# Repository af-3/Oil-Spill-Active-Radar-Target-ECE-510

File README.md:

# Oil-Spill-Active-Radar-Target-ECE-510
Cooperating radar target design for Portland State University ECE 510 winter 2016 Class<br>
[Radar Equations google Dock](https://docs.google.com/spreadsheets/d/1SBJ6qjm3yuyV2hIqerSS4fywFo_I5tQoiRfdYXWfvTU/pubhtml)

##Requirements
 * Must
   * Have a detection range of 10 meters
   * Be enviromentaly friendy specifically marine friendy
   * Build 8 working targets, but support at least 64 targets
   * Function correctly for at least 48 hours
   * Software must detect at least 64 targets
 * Should
   * Be no bigger then 3 X 3 X 2 inches
   * Have a detection range of 100 meters 
 * Could
   * Have smart tracking capability

##Additional Notes
 * Radar transmitter output power -6.02 dBm (.25 mW)
 * Radar operating frequincy is 2.304080 GHz
 * Antenna beam width on the vertical axis is about 68 digrees
 * Antenna beam width on the horizontal axis is about 52 digrees
 * Measured Receiver noise Floor is -120 dBm (10^-15 W)

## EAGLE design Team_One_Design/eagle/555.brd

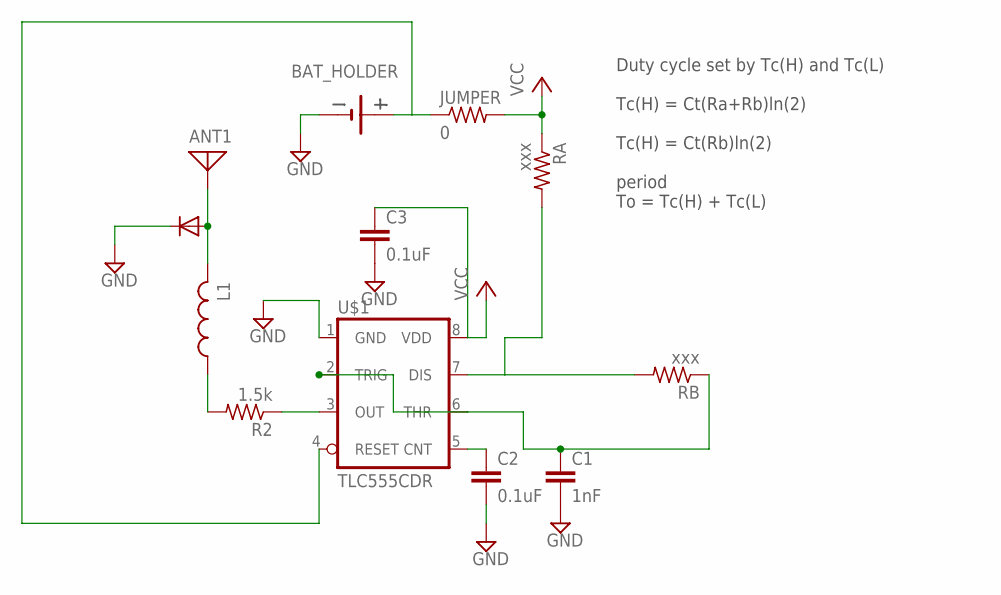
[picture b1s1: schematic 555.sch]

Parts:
ANT1: ANTENNA; PAD-01
C1: 1nF; C050-024X044
C2, C3: 0.1uF; C050-024X044
JUMPER: 0; R0805
L1: L-USL2012C; L2012C
R2: 1.5k; R0805
RA: xxx; R0805
RB: xxx; R0805
U$1: TLC555CDR; TLC555CRD
U$2: BAT_HOLDER
U$3: BAT-15-03W

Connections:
GND: C1.2, C2.2, C3.2, U$1.1 (GND), U$2.P_G2 (-), U$2.P_G3 (-), U$2.P_GND (-), U$3.C
unnamed: RA.2, RB.2, U$1.7 (DIS)
unnamed: R2.1, U$1.3 (OUT)
unnamed: JUMPER.1, U$1.4 (RESET), U$2.P_+ (+)
unnamed: C1.1, RB.1, U$1.2 (TRIG), U$1.6 (THR)
unnamed: C2.1, U$1.5 (CNT)
unnamed: L1.1, R2.2
unnamed: ANT1.1, L1.2, U$3.A
VCC: C3.1, JUMPER.2, RA.1, U$1.8 (VDD)

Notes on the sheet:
Duty cycle set by Tc(H) and Tc(L) Tc(H) = Ct(Ra+Rb)ln(2) Tc(H) = Ct(Rb)ln(2) period To = Tc(H) + Tc(L)

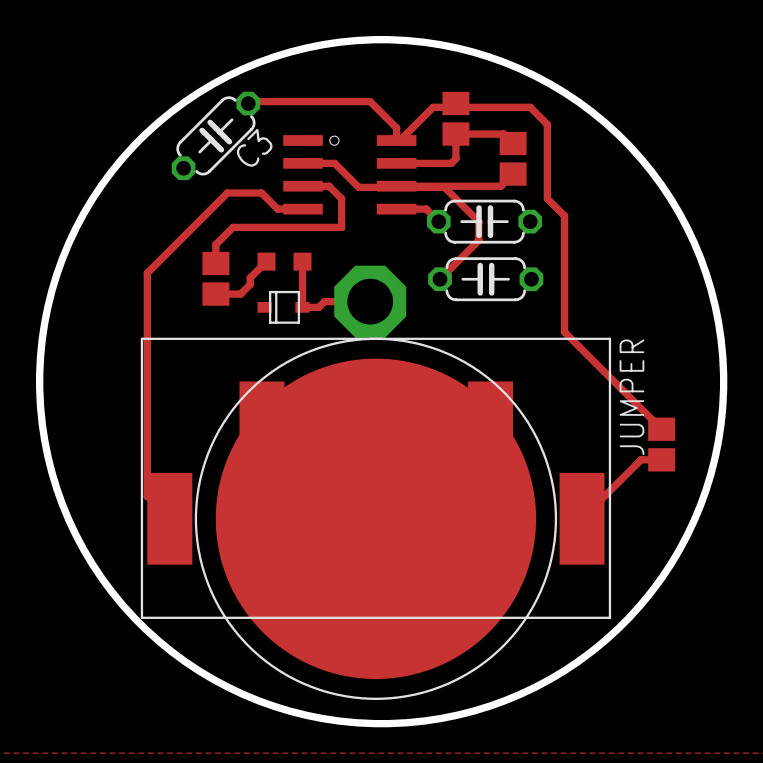
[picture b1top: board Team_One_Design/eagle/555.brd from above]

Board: 2 copper layers, 38.0 x 38.0 mm, 12 parts (0 on the bottom side), 9 nets.

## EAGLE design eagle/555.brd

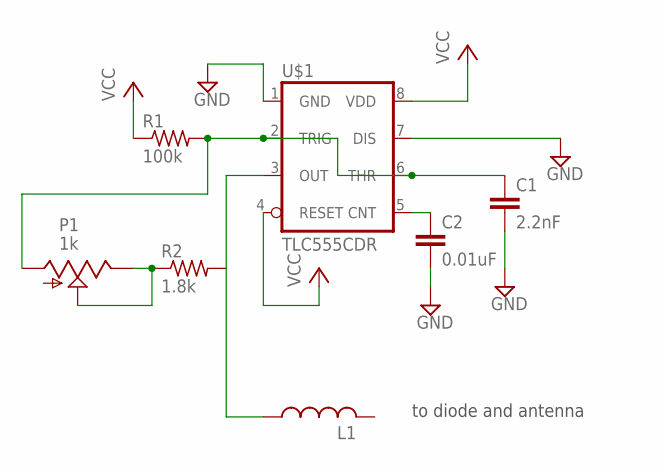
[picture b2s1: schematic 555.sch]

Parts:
C1: 2.2nF; C0805
C2: 0.01uF; C0805
L1: L-USL2012C; L2012C
P1: 1k; 3223J
R1: 100k; R0805
R2: 1.8k; R0805
U$1: TLC555CDR; TLC555CRD

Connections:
GND: C1.2, C2.2, U$1.1 (GND), U$1.7 (DIS)
unnamed: C1.1, P1.1 (A), R1.2, U$1.2 (TRIG), U$1.6 (THR)
unnamed: L1.1, R2.2, U$1.3 (OUT)
unnamed: P1.2 (S), P1.3 (E), R2.1
unnamed: C2.1, U$1.5 (CNT)
VCC: R1.1, U$1.4 (RESET), U$1.8 (VDD)

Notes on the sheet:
to diode and antenna

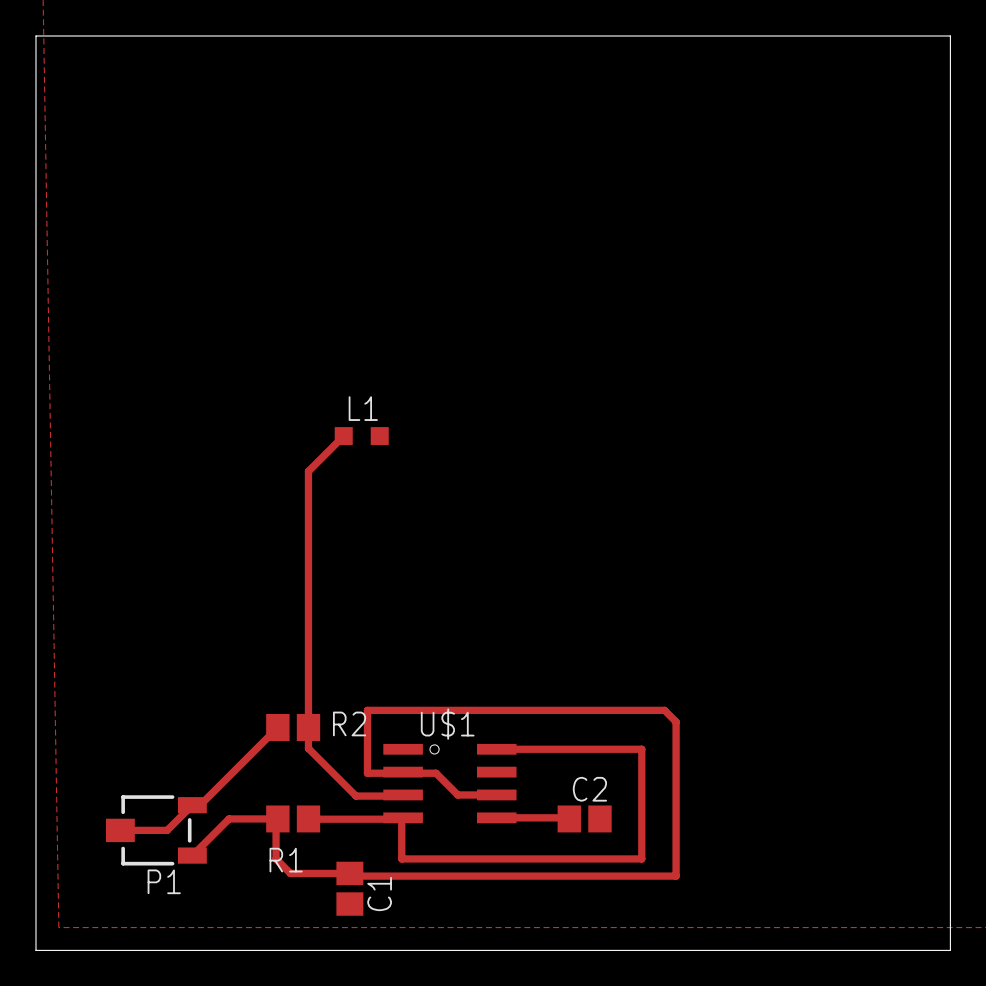
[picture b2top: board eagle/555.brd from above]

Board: 2 copper layers, 50.8 x 50.8 mm, 7 parts (0 on the bottom side), 6 nets.

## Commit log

2016-01-15 added an ltpisec simulation of the 555 timer. this circuit layout is set to 50 % duty cycle
2016-01-15 created eagle folder that will contain all eagle files for teh project, 510_library file should be used for all part libraries for the project
2016-01-15 added footprint for 555 timer
2016-01-15 created the TLC555CDR timmer part including schematic, layout
2016-01-21 changed footprint of TLC555CDR
2016-01-21 added datasheets and 555 target eagle schematic and layout
2016-01-24 Added initial version of beacon analysis
2016-01-29 Updated Readme
    Added new requirements from latest meeting
2016-02-02 mofified 555 timer schematic and layout
2016-02-03 Team Two LTSpice design
2016-02-04 Updated the analysis
2016-02-04 added datasheet for new RF diode, updated schem and layout for 555 circuit.
2016-02-08 Started working on spectrogram app
2016-02-09 Updated BOM
    added BOM with extended cost brake down
2016-02-10 Added thresholding of power
2016-02-11 Create EAGLE
2016-02-11 Update EAGLE
2016-02-11 Board and Schematic
2016-02-12 Canister 1
    Film Canister
2016-02-15 STL Files_Prototype 1
2016-02-16 KiCad files
    Added KiCad Project archive
    added board files
2016-02-18 updated schematic and layout of 555 timer board
2016-02-18 BOM
    Updated BOM
2016-02-18 BRD update
    Increased isolation electrolytic on capacitors
    Changed Battery Footprint
2016-02-29 added dimmesnsions to target layout
